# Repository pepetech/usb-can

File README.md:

# usb-can

This is an open source C++ library for use with the <a href="https://media.giphy.com/media/J0WeVOLjuqW2I/giphy.gif">USB-CAN</a> converter developed by Rafael Silva and João Silva

## Getting Started

These instructions will get you a copy of the project up and running on your local machine for development and testing purposes.

### Prerequisites

- You will need root access to a Linux machine.
- You will need to install development packages for libudev and libusb

- You will need the <a href="https://github.com/signal11/hidapi">hidapi</a> library installed 

- You will need to install libusb
```
sudo apt-get install libudev-dev libusb-1.0-0-dev
```

### Installing

A step by step series of examples that tell you how to get a development environment running

- Clone this repository to your working directory

```
sudo git clone https://github.com/Crying-Face-Emoji/MCP2210-CAN-sdk
```

- Go to the source directory

```
cd MCP2210-CAN-sdk/
```

- Run make

```
sudo make
```

## Running

- You may need to add the provided udev rules to the /etc/udev/rules.d directory.

```
sudo cp mcp2210-hid.rules /etc/udev/rules.d
```
- Depending on your user permissions, you might need to run the compilled binary with root access (sudo)

TODO: Explain how to run the automated tests for this system

## Authors

* **Rafael Silva** - *Initial work* - [crying-face-emoji](https://github.com/crying-face-emoji)
* **João Silva** - *Initial work* - [vankxr](https://github.com/vankxr)

See also the list of [contributors](https://github.com/Crying-Face-Emoji/MCP2210-CAN-sdk/graphs/contributors) who participated in this project.

## License

This project is licensed under the GNU General Public License v3.0 - see the [LICENSE.md](LICENSE.md) file for details

## Acknowledgments

* <a href="https://github.com/kerrydwong/MCP2210-Library">kerrydwong</a> - *mcp2210 library used as base*
* <a href="https://github.com/signal11/hidapi">signal11</a> - *original HID API*

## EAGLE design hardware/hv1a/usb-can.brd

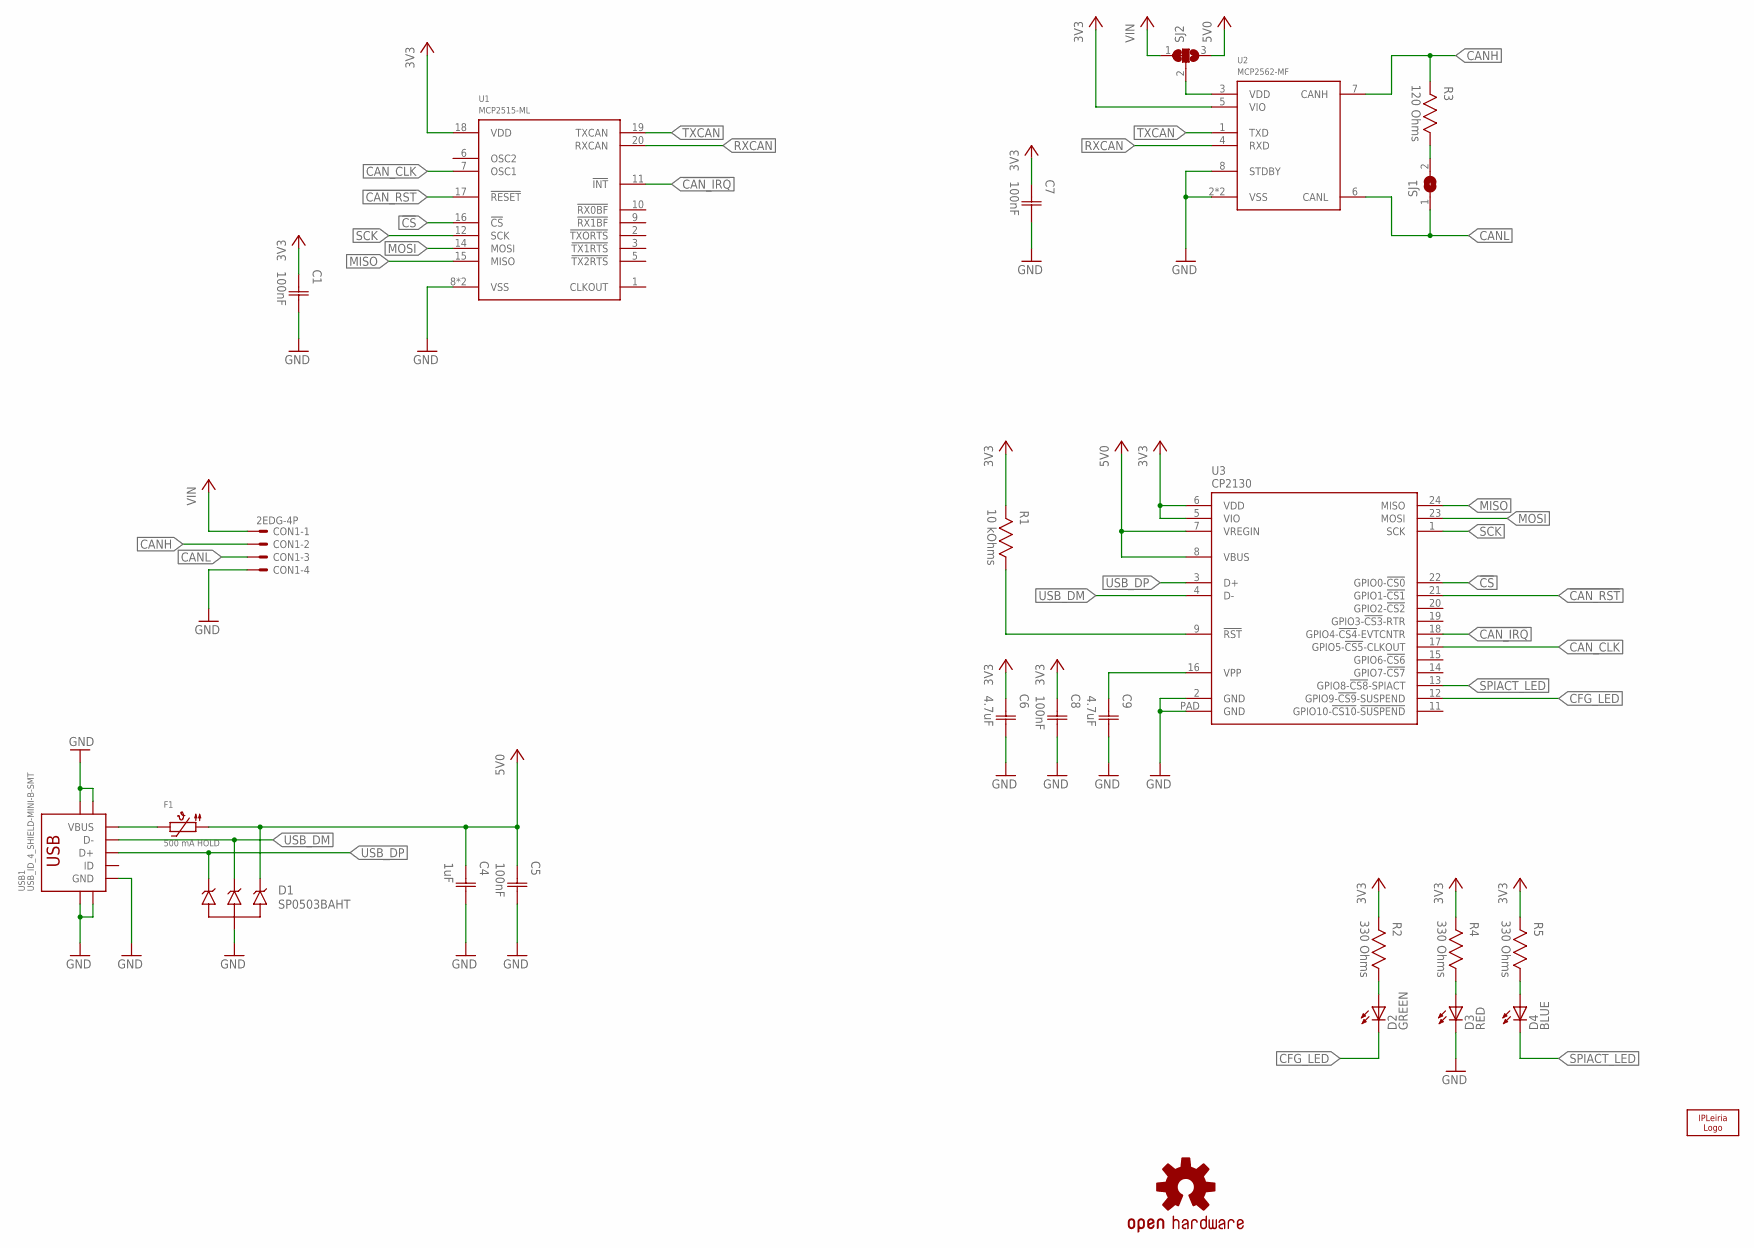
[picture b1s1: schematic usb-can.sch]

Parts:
C1, C5, C7, C8: 100nF; CAP0603
C4: 1uF; CAP0603
C6, C9: 4.7uF; CAP0603
CON1: 2EDG-4P
D1: SP0503BAHT; SOT143
D2: GREEN; 0603
D3: RED; 0603
D4: BLUE; 0603
F1: 500 mA HOLD; 1206
LOGO1: IPL-10MM; IPL_10MM
LOGO2: OSHW-LOGOM; OSHW-LOGO-M
R1: 10 kOhms; RES0603
R2, R4, R5: 330 Ohms; RES0603
R3: 120 Ohms; RES0603
SJ1: SJS; SJ_S
SJ2: SJ2CS; SJ2C_S
U1: MCP2515-ML; QFN20
U2: MCP2562-MF; DFN8
U3: CP2130; QFN24
USB1: USB_ID_4_SHIELD-MINI-B-SMT; USB-MB-S

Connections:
3V3: C1.1 (C1), C6.1 (C1), C7.1 (C1), C8.1 (C1), R1.2, R2.2, R4.2, R5.2, U1.18 (VDD), U2.5 (VIO), U3.5 (VIO), U3.6 (VDD)
5V0: C4.1 (C1), C5.1 (C1), D1.4, F1.1, SJ2.3, U3.7 (VREGIN), U3.8 (VBUS)
!CAN_IRQ: U1.11 (!INT!), U3.18 (GPIO4-!CS4!-EVTCNTR)
!CAN_RST: U1.17 (!RESET!), U3.21 (GPIO1-!CS1)
!CS: U1.16 (!CS!), U3.22 (GPIO0-!CS0)
CANH: CON1.P$2, R3.2, U2.7 (CANH)
CANL: CON1.P$3, SJ1.1, U2.6 (CANL)
CAN_CLK: U1.7 (OSC1), U3.17 (GPIO5-!CS5!-CLKOUT)
CFG_LED: D2.1 (C), U3.12 (GPIO9-!CS9!-SUSPEND)
GND: C1.2 (C2), C4.2 (C2), C5.2 (C2), C6.2 (C2), C7.2 (C2), C8.2 (C2), C9.2 (C2), CON1.P$4, D1.1, D3.1 (C), U1.8 (VSS), U1.PAD (VSS), U2.2 (VSS), U2.8 (STDBY), U2.9 (VSS), U3.2 (GND), U3.PAD (GND), USB1.GND, USB1.GND1 (SHIELD), USB1.GND2 (SHIELD), USB1.GND3 (SHIELD), USB1.GND4 (SHIELD)
MISO: U1.15 (MISO), U3.24 (MISO)
MOSI: U1.14 (MOSI), U3.23 (MOSI)
unnamed: SJ2.2, U2.3 (VDD)
unnamed: R3.1, SJ1.2
unnamed: C9.1 (C1), U3.16 (VPP)
unnamed: R1.1, U3.9 (!RST)
unnamed: F1.2, USB1.VBUS
unnamed: D3.2 (A), R4.1
unnamed: D4.2 (A), R5.1
unnamed: D2.2 (A), R2.1
RXCAN: U1.20 (RXCAN), U2.4 (RXD)
SCK: U1.12 (SCK), U3.1 (SCK)
SPIACT_LED: D4.1 (C), U3.13 (GPIO8-!CS8!-SPIACT)
TXCAN: U1.19 (TXCAN), U2.1 (TXD)
USB_DM: D1.3, U3.4 (D-), USB1.D-
USB_DP: D1.2, U3.3 (D+), USB1.D+
VIN: CON1.P$1, SJ2.1

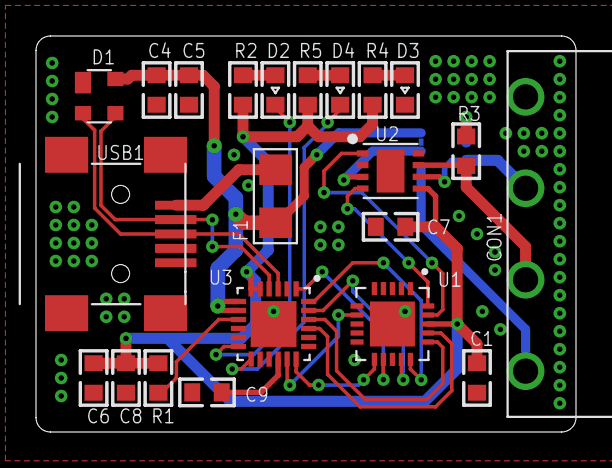
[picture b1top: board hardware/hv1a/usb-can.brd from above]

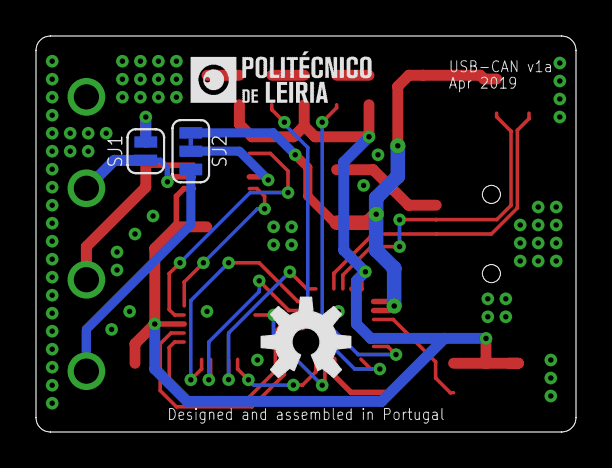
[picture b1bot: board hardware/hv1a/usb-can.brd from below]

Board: 2 copper layers, 30.0 x 22.0 mm, 26 parts (4 on the bottom side), 27 nets.

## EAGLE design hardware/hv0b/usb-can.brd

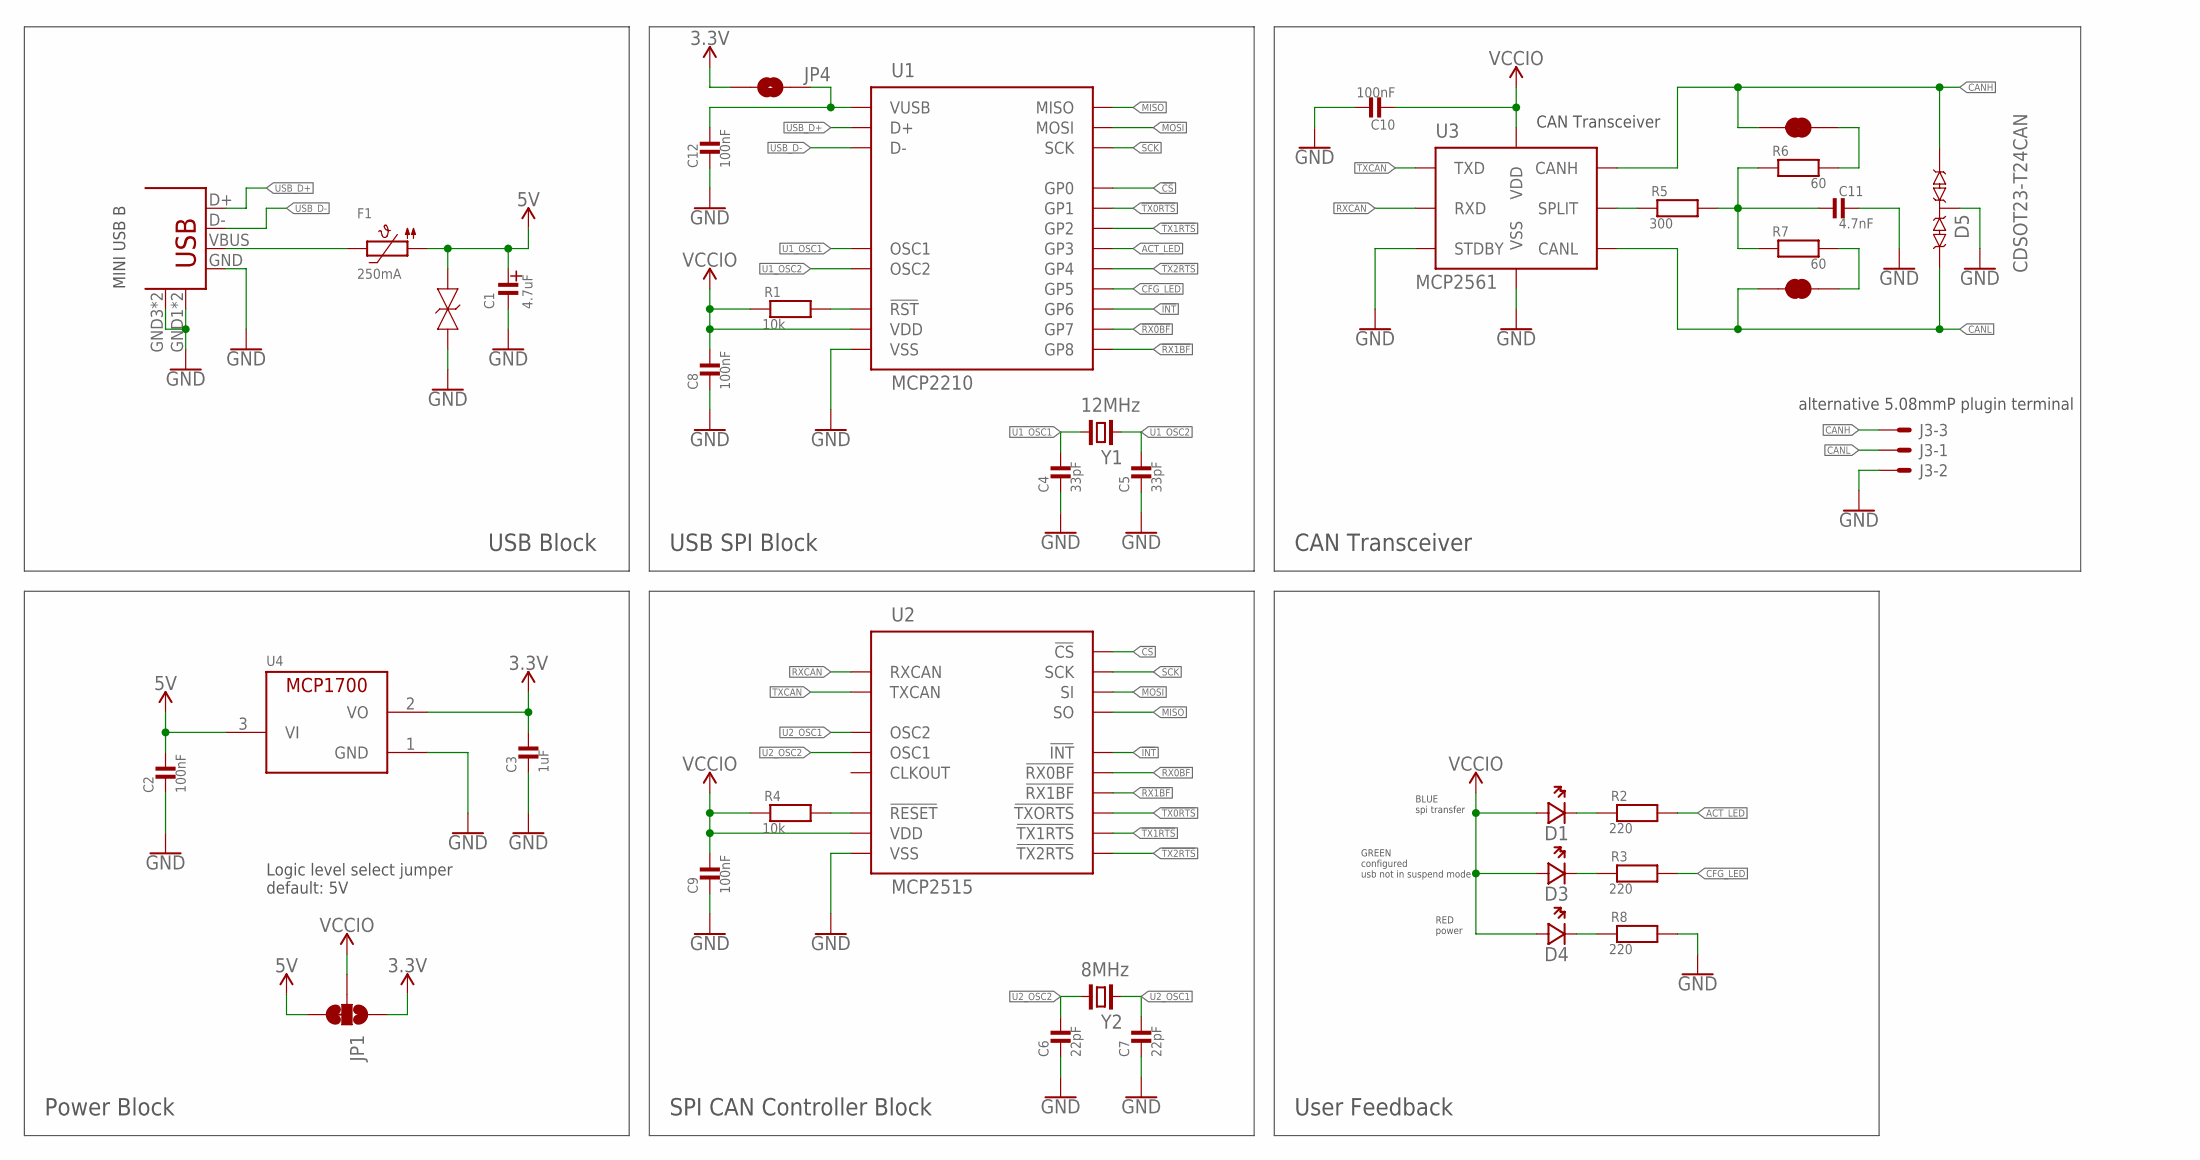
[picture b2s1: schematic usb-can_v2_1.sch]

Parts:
C1: 4.7uF; EIA3216
C2, C8, C9, C10, C12: 100nF; 0603_WAVE
C3: 1uF; 0603_WAVE
C4, C5: 33pF; 0603_WAVE
C6, C7: 22pF; 0603_WAVE
C11: 4.7nF; 0603_WAVE
D1: Blue; CHIPLED_0603
D2: PESD5V0S1BAF; SOD323
D3: Green; CHIPLED_0603
D4: Red; CHIPLED_0603
D5: CDSOT23-T24CAN; SOT-23-3
F1: 250mA; _1206
J2: USB_MINI_BMINIB; USB-MINIB
J3: 1X32EHGR; 2EHGR
JP1: JUMPER-SMT_3_1-NC_TRACE_SILK; SMT-JUMPER_3_1-NC_TRACE_SILK
JP2, JP3: JUMPER-SMT_2_NC_TRACE_SILK; SMT-JUMPER_2_NC_TRACE_SILK
JP4: JUMPER-SMT_2_NO_SILK; SMT-JUMPER_2_NO_SILK
R1, R4: 10k; 0603_WAVE
R2, R3, R8: 220; 0603_WAVE
R5: 300; 0603_WAVE
R6, R7: 60; 0603_WAVE
U1: MCP2210; SOIC-20_300MIL
U2: MCP2515; SOIC-18_300MIL
U3: MCP2561; SOIC_8
U4: 250mA; SOT-23
Y1: 12MHz; 2-SMD-5X3
Y2: 8MHz; 2-SMD-5X3

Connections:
3.3V: C3.P$1, JP1.1, JP4.2, U4.2 (VO)
5V: C1.+ (AN), C2.P$1, D2.P$1, F1.1, JP1.3, U4.3 (VI)
!CS: U1.P$5 (GP0), U2.P$16 (!CS!)
!INT: U1.P$14 (GP6), U2.P$12 (!INT!)
!RX0BF: U1.P$15 (GP7), U2.P$11 (!RX0BF!)
!RX1BF: U1.P$16 (GP8), U2.P$10 (!RX1BF!)
!TX0RTS: U1.P$6 (GP1), U2.P$4 (!TXORTS!)
!TX1RTS: U1.P$7 (GP2), U2.P$5 (!TX1RTS!)
!TX2RTS: U1.P$10 (GP4), U2.P$6 (!TX2RTS!)
ACT_LED: R2.P$2, U1.P$8 (GP3)
CANH: D5.P$2 (2), J3.P$3, JP3.2, U3.P$7 (CANH)
CANL: D5.P$1 (1), J3.P$1, JP2.2, U3.P$6 (CANL)
CFG_LED: R3.P$2, U1.P$12 (GP5)
GND: C1.- (CA), C2.P$2, C3.P$2, C4.P$2, C5.P$2, C6.P$2, C7.P$2, C8.P$2, C9.P$2, C10.P$1, C11.P$1, C12.P$2, D2.P$2, D5.P$3 (3), J2.GND, J2.GND1, J2.GND2, J2.GND3, J2.GND4, J3.P$2, R8.P$2, U1.P$20 (VSS), U2.P$9 (VSS), U3.P$2 (VSS), U3.P$8 (STDBY), U4.1 (GND)
MISO: U1.P$13 (MISO), U2.P$15 (SO)
MOSI: U1.P$9 (MOSI), U2.P$14 (SI)
unnamed: JP2.1, R7.P$2
unnamed: D1.C (CA), R2.P$1
unnamed: D3.C (CA), R3.P$1
unnamed: R1.P$2, U1.P$4 (!RST!)
unnamed: R4.P$2, U2.P$17 (!RESET!)
unnamed: D4.C (CA), R8.P$1
unnamed: JP3.1, R6.P$2
unnamed: F1.2, J2.VBUS
unnamed: C12.P$1, JP4.1, U1.P$17 (VUSB)
unnamed: C11.P$2, R5.P$2, R6.P$1, R7.P$1
unnamed: R5.P$1, U3.P$5 (SPLIT)
RXCAN: U2.P$2 (RXCAN), U3.P$4 (RXD)
SCK: U1.P$11 (SCK), U2.P$13 (SCK)
TXCAN: U2.P$1 (TXCAN), U3.P$1 (TXD)
U1_OSC1: C4.P$1, U1.P$2 (OSC1), Y1.1
U1_OSC2: C5.P$1, U1.P$3 (OSC2), Y1.2
U2_OSC1: C7.P$1, U2.P$7 (OSC2), Y2.2
U2_OSC2: C6.P$1, U2.P$8 (OSC1), Y2.1
USB_D+: J2.D+, U1.P$19 (D+)
USB_D-: J2.D-, U1.P$18 (D-)
VCCIO: C8.P$1, C9.P$1, C10.P$2, D1.A (AN), D3.A (AN), D4.A (AN), JP1.2, R1.P$1, R4.P$1, U1.P$1 (VDD), U2.P$18 (VDD), U3.P$3 (VDD)

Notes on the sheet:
BLUE spi transfer
GREEN configured usb not in suspend mode
RED power
alternative 5.08mmP plugin terminal
CAN Transceiver
MINI USB B
Logic level select jumper default: 5V
Power Block
USB Block
USB SPI Block
SPI CAN Controller Block
User Feedback

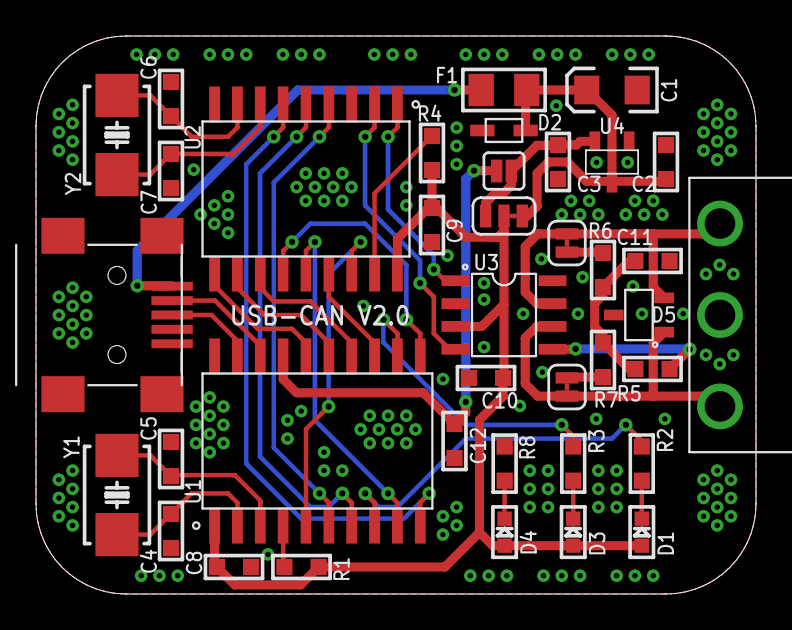
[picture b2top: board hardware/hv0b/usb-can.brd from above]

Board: 2 copper layers, 40.0 x 31.0 mm, 38 parts (0 on the bottom side), 37 nets.

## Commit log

2018-11-21 Remove unnecessary files
2018-11-21 First try mixing MCP2210 witn MCP2515
2018-11-21 Makefile edit
2018-11-21 Fix errors
2018-11-21 Fix errors 2
2018-11-21 Fix errors 3
2018-11-21 Makefile edit 1
2018-11-21 Makefile 2
2018-11-21 guardatings
2018-11-21 xis de
2018-11-21 xd look there
2018-11-21 xis de dois
2018-11-21 smd twice bitch
2018-11-21 send msg
2018-11-21 include time
2018-11-22 Updated makefile
2018-11-22 Update Makefile
2018-11-28 Success!
2019-02-10 Remove useless Atom shit
    b1g vs code
2019-02-10 Set SPI clock back to 10 MHz
    Was 1 MHz for testing
2019-02-19 It twerks!
2019-02-19 "send receive"
2019-03-08 Update README.md
    Reformatting and adding missing commands (HID rules copy)
2019-03-29 changed project structure, consolidated project files
2019-03-29 start cp2130 layer
2019-03-30 Organize and add v1a sch
2019-04-02 Work
2019-04-03 Commit to update
2019-04-03 added files in preparation for sfv1a development
2019-04-04 Work on PCB
2019-04-04 Change MCP2515 lib to use CP2130
2019-04-04 Add gitignore to vs code path and remove useless files
2019-04-04 Hardware v1a completed
2019-04-04 Center text
2019-04-04 fixed bug in sv0a
2019-04-10 Add more vias and generate gerbers
2019-04-14 added license file
2019-04-14 added license
2019-05-07 Added eagle project file

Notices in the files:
parts and their libraries:
SparkFun: Licensing: CC v3.0 Share-Alike You are welcome to use this library for commercial purposes.
SparkFun-PowerSymbols: Licensing: Creative Commons ShareAlike 4.0 International - https://creativecommons.org/licenses/by-sa/4.0
SparkFun-Aesthetics: https://creativecommons.org/licenses/by-sa/4.0
